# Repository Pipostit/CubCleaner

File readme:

# Goal
This project aim to repair a broken vacuum cleaner (Taurus : UNLIMITED 29.0 LITHIUM)
- Battery and PCB are dead. I suspect a short on the mainboard
- Solution: Redo the pcb and the battery pack

8 li-on cell were used in the original holder, an BMs is used outside of the scope of this design (https://www.aliexpress.com/item/1005004441321493.html)

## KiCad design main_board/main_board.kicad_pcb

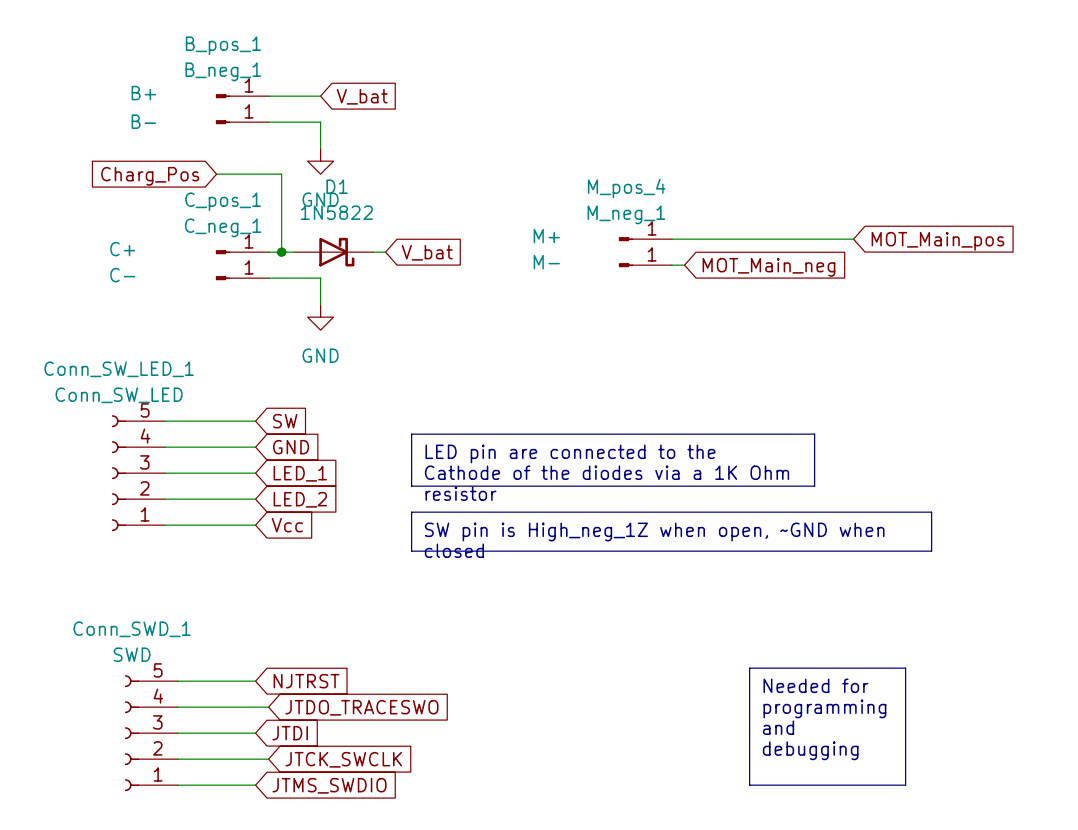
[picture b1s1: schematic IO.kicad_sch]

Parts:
B_neg_1: B-; SolderWire-1.5sqmm_1x01_D1.7mm_OD3.9mm
B_pos_1: B+; SolderWire-1.5sqmm_1x01_D1.7mm_OD3.9mm
C_neg_1: C-; SolderWire-1.5sqmm_1x01_D1.7mm_OD3.9mm
C_pos_1: C+; SolderWire-1.5sqmm_1x01_D1.7mm_OD3.9mm
Conn_SWD_1: SWD; JST_XH_S5B-XH-A-1_1x05_P2.50mm_Horizontal
Conn_SW_LED_1: Conn_SW_LED; JST_XH_S5B-XH-A-1_1x05_P2.50mm_Horizontal
D1: 1N5822; D_SMA
M_neg_1: M-; SolderWire-1.5sqmm_1x01_D1.7mm_OD3.9mm
M_pos_4: M+; SolderWire-1.5sqmm_1x01_D1.7mm_OD3.9mm

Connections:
Charg_Pos: C_pos_1.1, D1.2 (A)
GND: B_neg_1.1, C_neg_1.1, Conn_SW_LED_1.4; also elsewhere on the board
JTCK_SWCLK: Conn_SWD_1.2; also elsewhere on the board
JTDI: Conn_SWD_1.3; also elsewhere on the board
JTDO_TRACESWO: Conn_SWD_1.4; also elsewhere on the board
JTMS_SWDIO: Conn_SWD_1.1; also elsewhere on the board
MOT_Main_neg: M_neg_1.1; also elsewhere on the board
MOT_Main_pos: M_pos_4.1; also elsewhere on the board
NJTRST: Conn_SWD_1.5; also elsewhere on the board
SW: Conn_SW_LED_1.5; also elsewhere on the board
V_bat: B_pos_1.1, D1.1 (K); also elsewhere on the board
Vcc: Conn_SW_LED_1.1; also elsewhere on the board

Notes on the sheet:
Needed for programming and debugging
SW pin is High_neg_1Z when open, ~GND when closed
LED pin are connected to the Cathode of the diodes via a 1K Ohm resistor

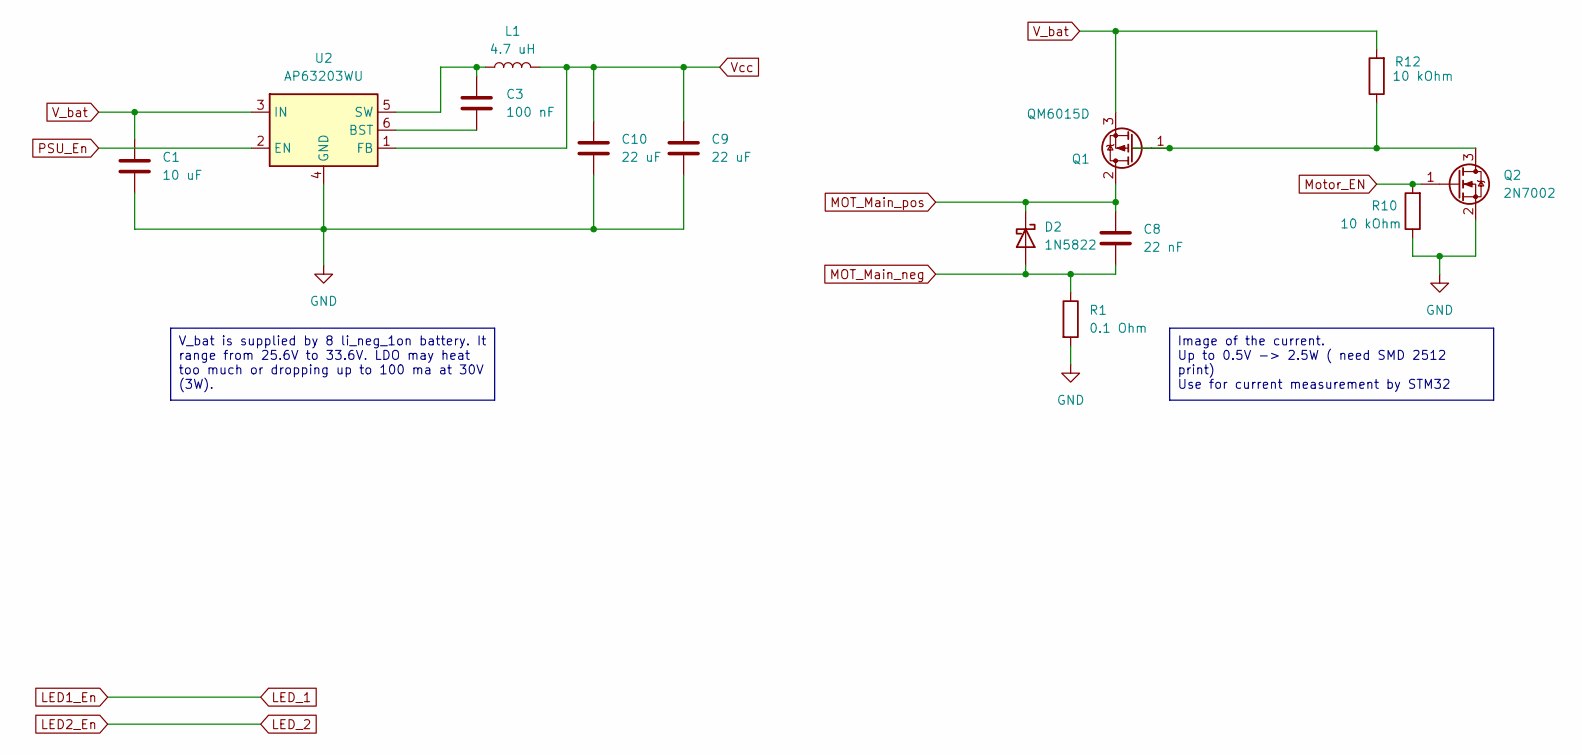
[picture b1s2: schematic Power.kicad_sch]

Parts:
C1: 10 uF; C_1206_3216Metric_Pad1.33x1.80mm_HandSolder
C3: 100 nF; C_0201_0603Metric_Pad0.64x0.40mm_HandSolder
C8: 22 nF; C_0603_1608Metric_Pad1.08x0.95mm_HandSolder
C9, C10: 22 uF; C_0603_1608Metric_Pad1.08x0.95mm_HandSolder
D2: 1N5822; D_SMA
L1: 4.7 uH; L_0603_1608Metric_Pad1.05x0.95mm_HandSolder
Q1: QM6015D; TO-252-2
Q2: 2N7002; SOT-23
R1: 0.1 Ohm; R_2512_6332Metric_Pad1.40x3.35mm_HandSolder
R10, R12: 10 kOhm; R_0201_0603Metric_Pad0.64x0.40mm_HandSolder
U2: AP63203WU; TSOT-23-6

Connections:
GND: C1.2, C9.2, C10.2, Q2.2 (S), R1.2, R10.1, U2.4 (GND); also elsewhere on the board
MOT_Main_neg: C8.2, D2.2 (A), R1.1; also elsewhere on the board
MOT_Main_pos: C8.1, D2.1 (K), Q1.2 (D); also elsewhere on the board
Motor_EN: Q2.1 (G), R10.2; also elsewhere on the board
unnamed: Q1.1 (G), Q2.3 (D), R12.1
unnamed: C3.2, U2.6 (BST)
unnamed: C3.1, L1.1, U2.5 (SW)
PSU_En: U2.2 (EN); also elsewhere on the board
V_bat: C1.1, Q1.3 (S), R12.2, U2.3 (IN); also elsewhere on the board
Vcc: C9.1, C10.1, L1.2, U2.1 (FB); also elsewhere on the board

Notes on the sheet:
V_bat is supplied by 8 li_neg_1on battery. It range from 25.6V to 33.6V. LDO may heat too much or dropping up to 100 ma at 30V (3W).
Image of the current. Up to 0.5V -> 2.5W ( need SMD 2512 print) Use for current measurement by STM32

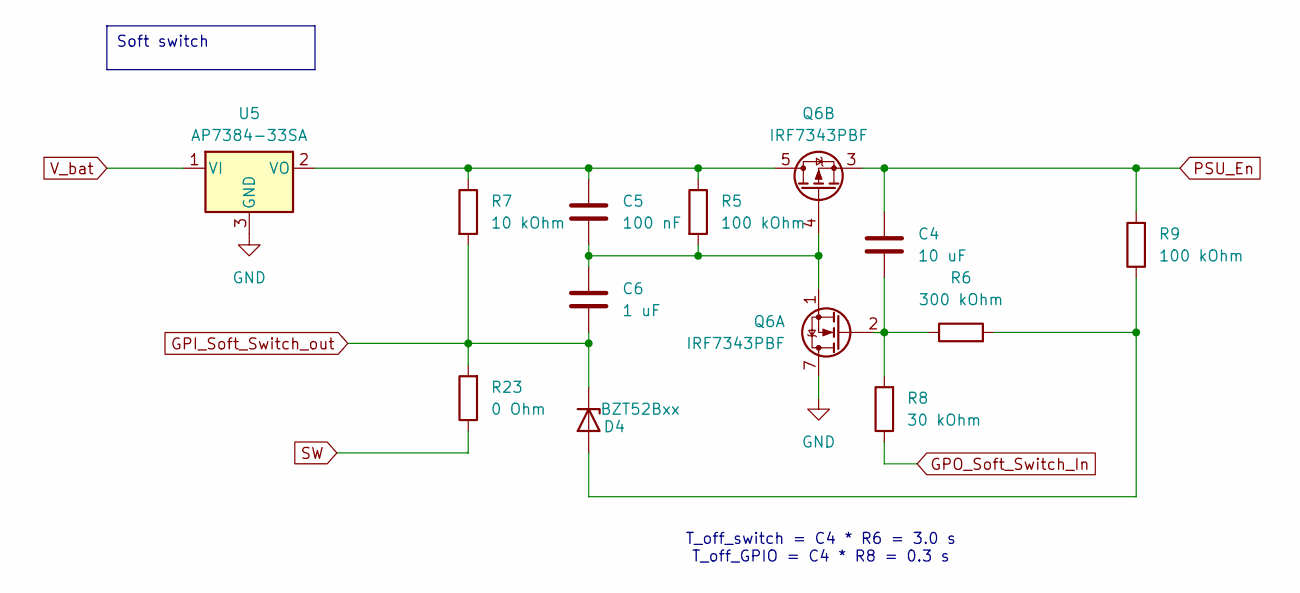
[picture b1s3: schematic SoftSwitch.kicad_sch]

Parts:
C4: 10 uF; C_0603_1608Metric_Pad1.08x0.95mm_HandSolder
C5: 100 nF; C_0201_0603Metric_Pad0.64x0.40mm_HandSolder
C6: 1 uF; C_0402_1005Metric_Pad0.74x0.62mm_HandSolder
D4: BZT52Bxx; D_SOD-123F
Q6: IRF7343PBF; SOIC-8_3.9x4.9mm_P1.27mm
R5, R9: 100 kOhm; R_0201_0603Metric_Pad0.64x0.40mm_HandSolder
R6: 300 kOhm; R_0201_0603Metric_Pad0.64x0.40mm_HandSolder
R7: 10 kOhm; R_0201_0603Metric_Pad0.64x0.40mm_HandSolder
R8: 30 kOhm; R_0201_0603Metric_Pad0.64x0.40mm_HandSolder
R23: 0 Ohm; R_0201_0603Metric_Pad0.64x0.40mm_HandSolder
U5: AP7384-33SA; SOT-23

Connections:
GND: Q6.7 (D), Q6.8 (D), U5.3 (GND); also elsewhere on the board
GPI_Soft_Switch_out: C6.1, D4.1 (K), R7.2, R23.2; also elsewhere on the board
GPO_Soft_Switch_In: R8.1; also elsewhere on the board
unnamed: D4.2 (A), R6.2, R9.1
unnamed: C4.1, Q6.2 (G), R6.1, R8.2
unnamed: C5.2, C6.2, Q6.1 (S), Q6.4 (G), R5.2
unnamed: C5.1, Q6.5 (D), Q6.6 (D), R5.1, R7.1, U5.2 (VO)
PSU_En: C4.2, Q6.3 (1), R9.2; also elsewhere on the board
SW: R23.1; also elsewhere on the board
V_bat: U5.1 (VI); also elsewhere on the board

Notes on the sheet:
Soft switch
T_off_switch = C4 * R6 = 3.0 s T_off_GPIO = C4 * R8 = 0.3 s

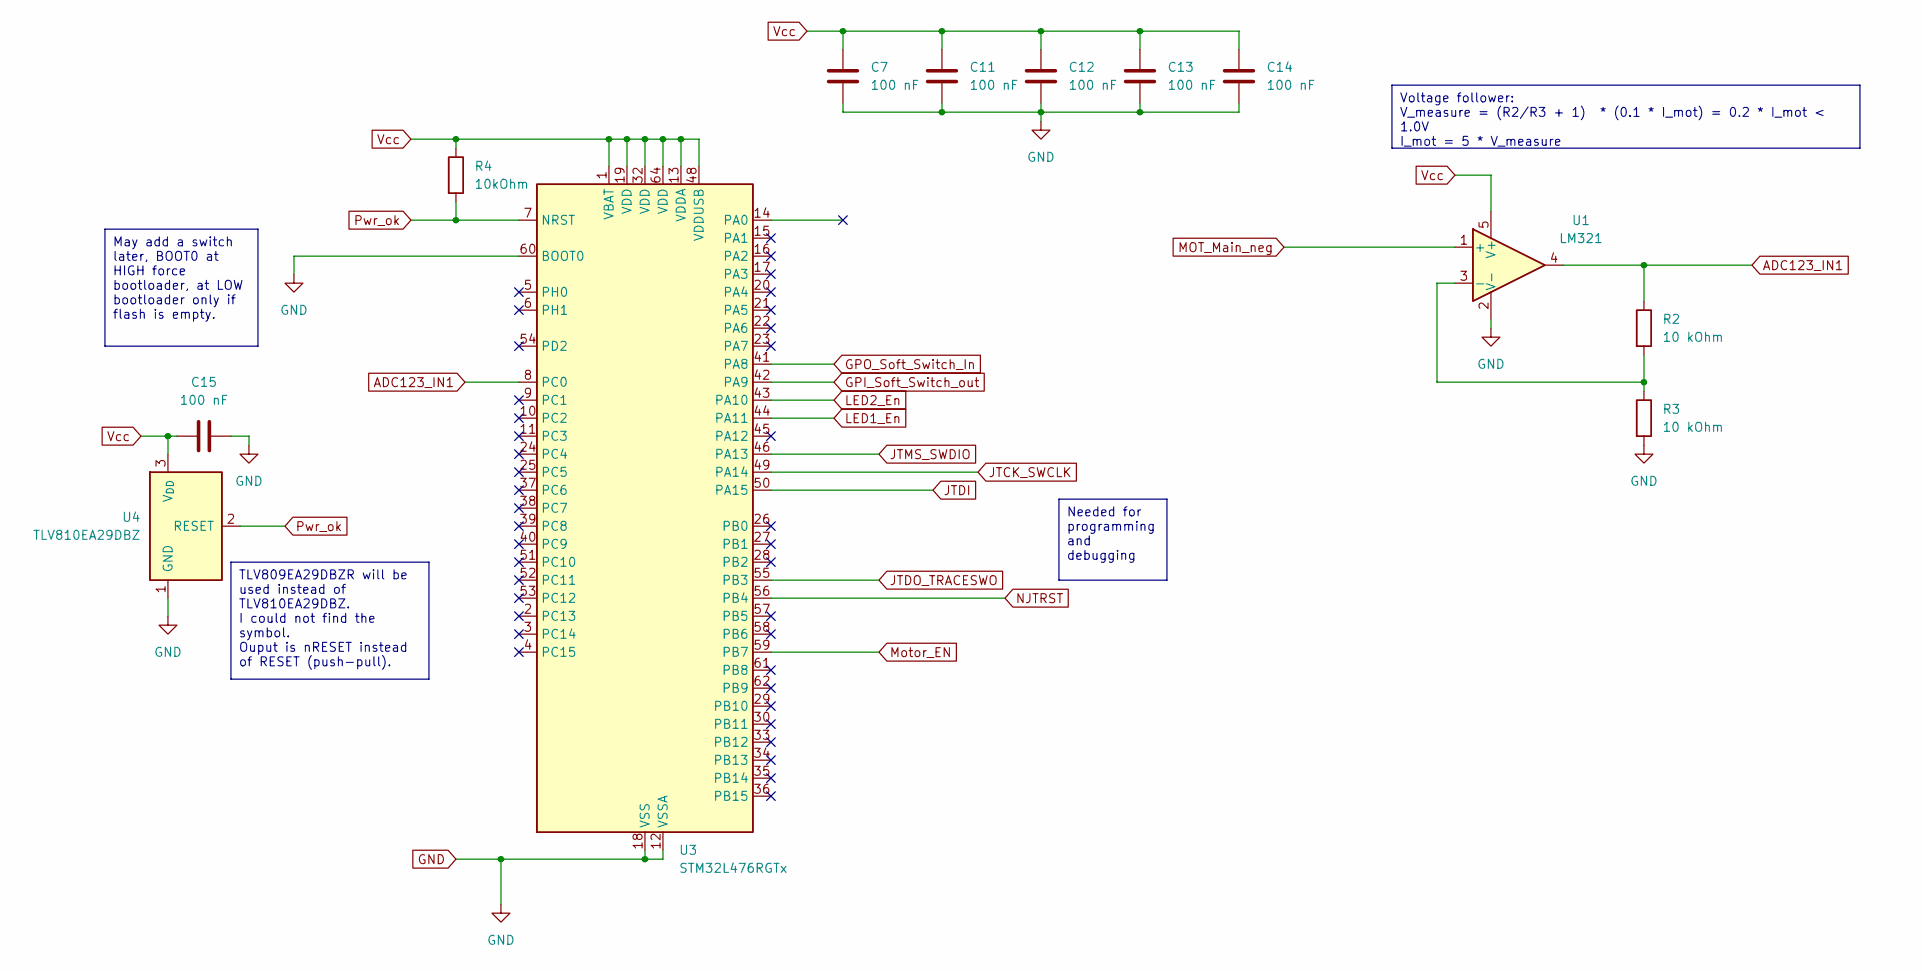
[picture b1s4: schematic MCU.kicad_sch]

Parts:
C7, C11, C12, C13, C14, C15: 100 nF; C_0201_0603Metric_Pad0.64x0.40mm_HandSolder
R2, R3: 10 kOhm; R_0201_0603Metric
R4: 10kOhm; R_0201_0603Metric_Pad0.64x0.40mm_HandSolder
U1: LM321; SOT-23-5
U3: STM32L476RGTx; LQFP-64_10x10mm_P0.5mm
U4: TLV810EA29DBZ; SOT-23

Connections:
ADC123_IN1: R2.1, U1.4, U3.8 (PC0)
GND: C7.2, C11.2, C12.2, C13.2, C14.2, C15.2, R3.2, U1.2 (V-), U3.12 (VSSA), U3.18 (VSS), U3.31 (VSS), U3.47 (VSS), U3.60 (BOOT0), U3.63 (VSS), U4.1 (GND); also elsewhere on the board
GPI_Soft_Switch_out: U3.42 (PA9); also elsewhere on the board
GPO_Soft_Switch_In: U3.41 (PA8); also elsewhere on the board
JTCK_SWCLK: U3.49 (PA14); also elsewhere on the board
JTDI: U3.50 (PA15); also elsewhere on the board
JTDO_TRACESWO: U3.55 (PB3); also elsewhere on the board
JTMS_SWDIO: U3.46 (PA13); also elsewhere on the board
MOT_Main_neg: U1.1 (+); also elsewhere on the board
Motor_EN: U3.59 (PB7); also elsewhere on the board
NJTRST: U3.56 (PB4); also elsewhere on the board
unnamed: R2.2, R3.1, U1.3 (-)
Pwr_ok: R4.2, U3.7 (NRST), U4.2 (RESET)
Vcc: C7.1, C11.1, C12.1, C13.1, C14.1, C15.1, R4.1, U1.5 (V+), U3.1 (VBAT), U3.13 (VDDA), U3.19 (VDD), U3.32 (VDD), U3.48 (VDDUSB), U3.64 (VDD), U4.3 (V_{DD}); also elsewhere on the board

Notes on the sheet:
Needed for programming and debugging
Voltage follower: V_measure = (R2/R3 + 1) * (0.1 * I_mot) = 0.2 * I_mot < 1.0V I_mot = 5 * V_measure
May add a switch later, BOOT0 at HIGH force bootloader, at LOW bootloader only if flash is empty.
TLV809EA29DBZR will be used instead of TLV810EA29DBZ. I could not find the symbol. Ouput is nRESET instead of RESET (push-pull).

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
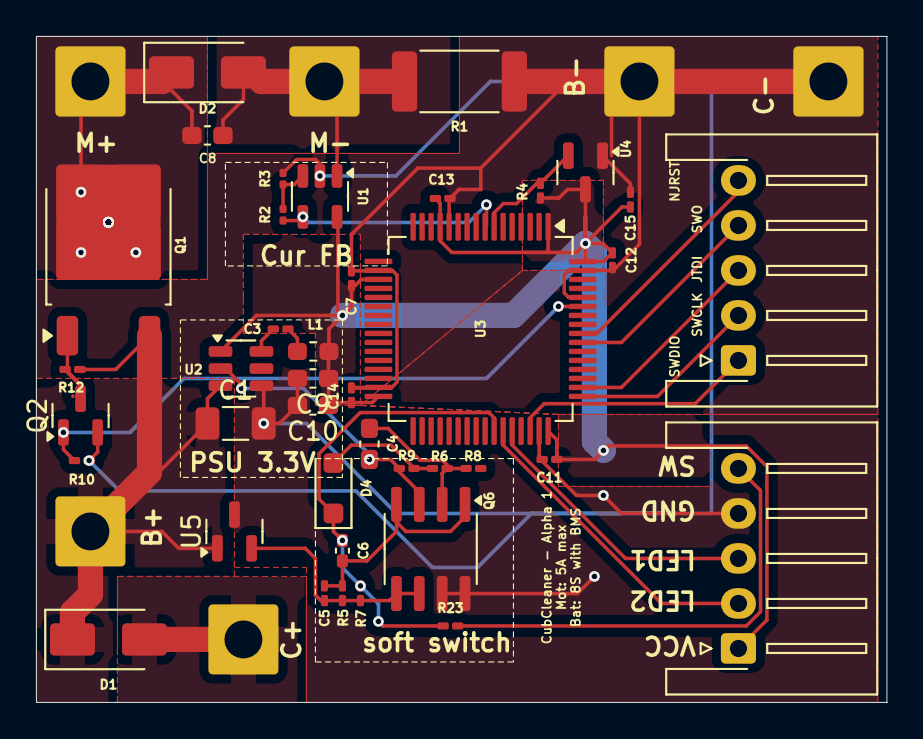
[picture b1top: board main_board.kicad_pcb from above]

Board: 2 copper layers, 47.2 x 37.0 mm, 46 parts (0 on the bottom side), 28 nets.

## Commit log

2025-01-05 Initial commit: -gitignore -Readme
2025-01-05 First iteration of the PCB
2025-01-05 Change JST connector for horizontal connector, reuse JST connector for debugging, correct pin order.
2025-01-06 Replace voltage comparator with dedicated voltage supervisor, add motor current measurement
2025-01-11 WIP: Ensure that no 30V can attain the MCU IO, change passiv component size to match value
